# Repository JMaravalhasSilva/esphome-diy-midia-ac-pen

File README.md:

# ESPHome DIY Midea AC Pen
## An easy to make wifi pen to control Midea AC units

This repo contains the files to make a wifi pen to control Midea AC units using the [ESPHome Midea component](https://esphome.io/components/climate/midea/).

The pen uses only a handful of components which are extremelly easy to obtain, and extremelly easy to solder as well!

Bill of materials: 
 - x1 ESP32 C3 Super Mini board
 - x2 2N3904 Transistors
 - x4 10kOhm Resistors
 - x1 Male USB connector

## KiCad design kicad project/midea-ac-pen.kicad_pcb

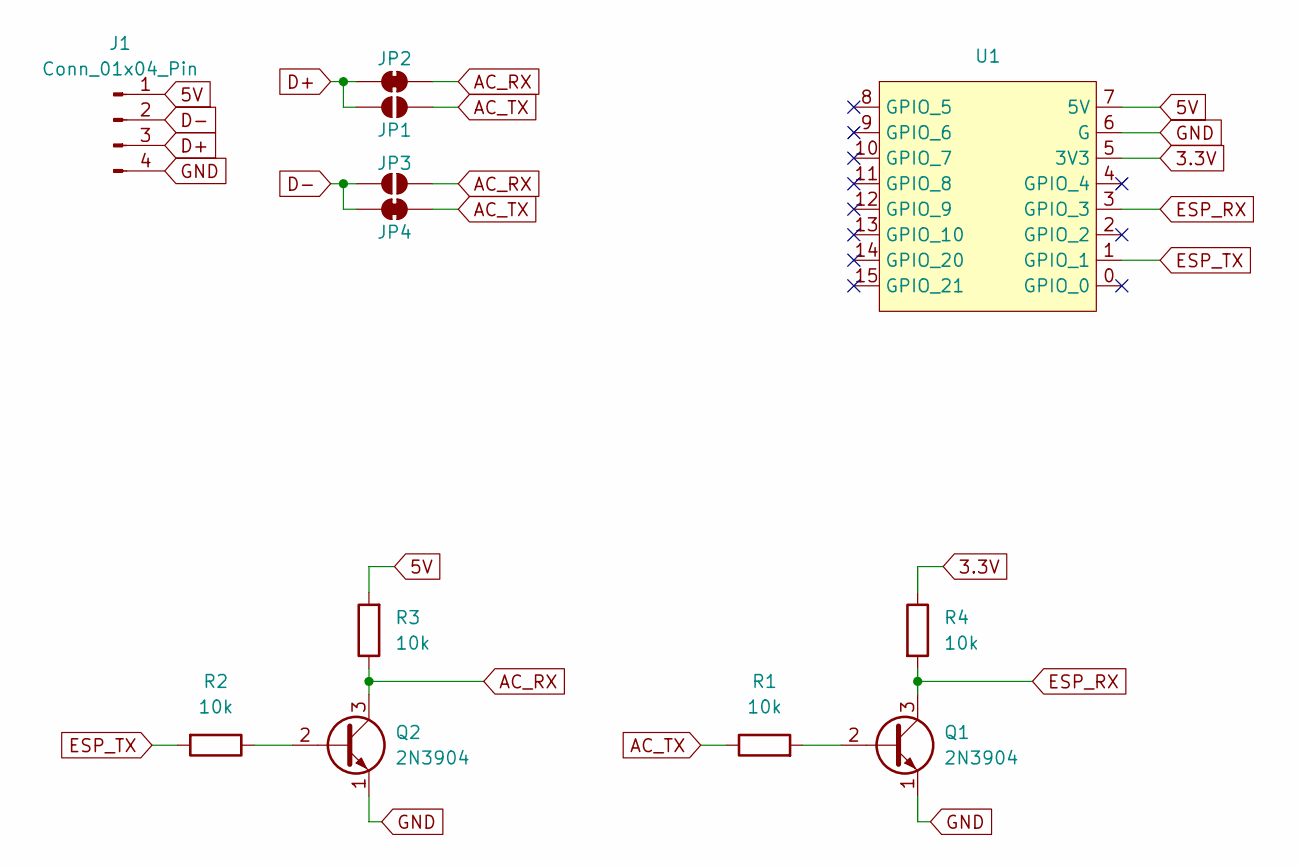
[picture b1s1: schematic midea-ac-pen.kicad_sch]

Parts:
J1: Conn_01x04_Pin; PCB_USB
JP1, JP3: SolderJumper_2_Open; SolderJumper-2_P1.3mm_Open_RoundedPad1.0x1.5mm
JP2, JP4: SolderJumper_2_Bridged; SolderJumper-2_P1.3mm_Bridged_RoundedPad1.0x1.5mm
Q1, Q2: 2N3904; TO-92
R1, R2, R3, R4: 10k; R_Axial_DIN0204_L3.6mm_D1.6mm_P2.54mm_Vertical
U1: ESP32_C3_Super_Mini

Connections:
3.3V: R4.1, U1.5 (3V3)
5V: J1.1, R3.2, U1.7 (5V)
AC_RX: JP2.2 (B), JP3.1 (A), Q2.3 (C), R3.1
AC_TX: JP1.1 (A), JP4.2 (B), R1.1
D+: J1.3, JP1.2 (B), JP2.1 (A)
D-: J1.2, JP3.2 (B), JP4.1 (A)
ESP_RX: Q1.3 (C), R4.2, U1.3 (GPIO_3)
ESP_TX: R2.2, U1.1 (GPIO_1)
GND: J1.4, Q1.1 (E), Q2.1 (E), U1.6 (G)
unnamed: Q1.2 (B), R1.2
unnamed: Q2.2 (B), R2.1

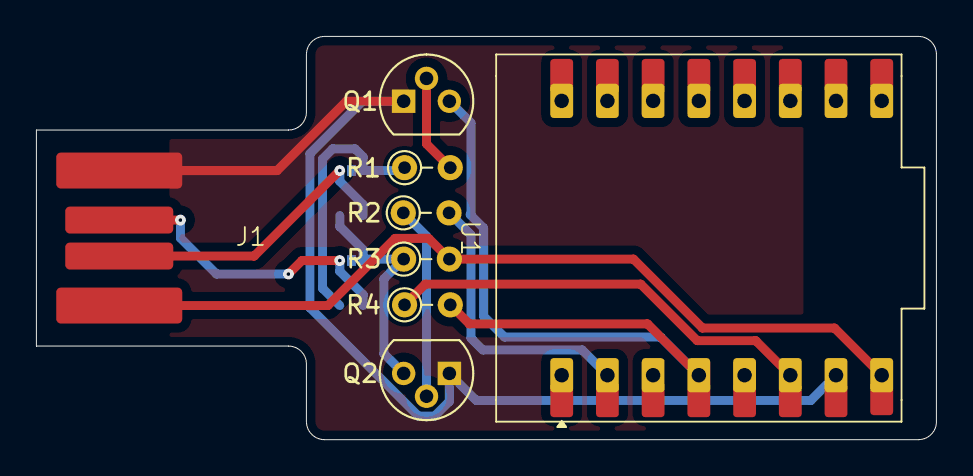
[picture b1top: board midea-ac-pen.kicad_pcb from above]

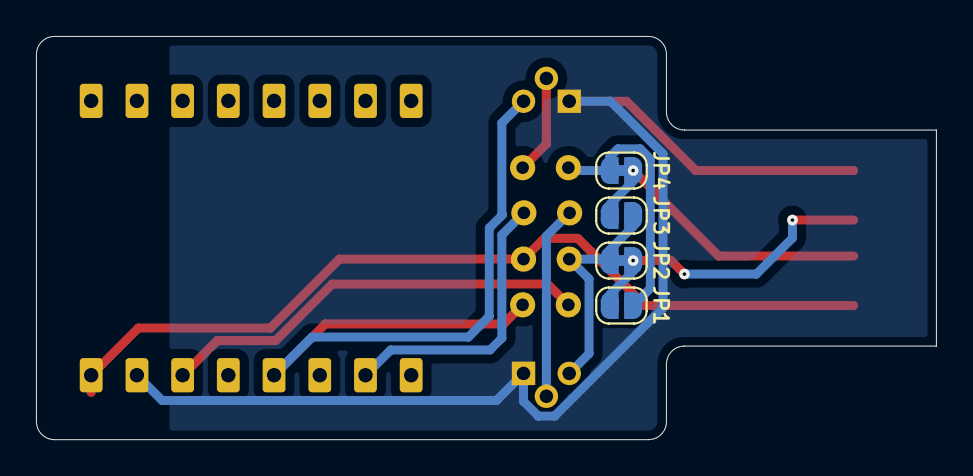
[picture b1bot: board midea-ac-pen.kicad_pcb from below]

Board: 2 copper layers, 50.0 x 22.4 mm, 12 parts (4 on the bottom side), 11 nets.

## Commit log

2025-09-12 Create initial schematic
2025-09-12 draw pcb
2025-09-12 Fix library names and remove value field from ESP32 symbol
2025-09-12 Finish board design
2025-11-13 Fix typos in README.md
